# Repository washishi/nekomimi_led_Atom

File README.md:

# Nekomimi LED  for Atom
M5StackのAtomシリーズ用(AtomU/S3U以外)のネコミミ型LED基板です  
NeoPixel(WS2812)互換の1mmx1mmサイズのRGB LEDが左右に9個ずつ合計18個付いており独立して色や明るさ等を制御することができます  

## 使い方
M5Stack Atomシリーズ裏面のピンソケットに本基盤のピン部分を差し込んで取り付けます

### 使用するGPIO（ピン）

使用するGPIO端子は上記写真の赤枠のランドいずれかをはんだでショートすることにより選択できます  
[BOOTH](https://washishi.booth.pm/)等で頒布するものは上記写真のように右側上から２番目の端子が既にショートされています  
その場合の利用するGPIOは下記となります  
|Atom種別|LED Data Out|
|:--|:-:|  
|AtomS3/S3R/S3Lite/S3RCAM/S3REx/EchoS3R等S3系|G38|
|AtomLite/AtomMatrix/AtomEcho等S3系以外|G25|

## ソフトウエアでの利用について
Arduino IDE や VSCode + PlatformIO で利用する場合は
[FastLED](https://github.com/FastLED/FastLED)や[Adafruit NeoPixel](https://github.com/adafruit/Adafruit_NeoPixel)等のライブラリで利用できます  
UIFlowで利用する場合はHardwareでRGBを追加し利用するGPIOとLEDの数18を指定すれば利用できます  
その他に関しても NeoPixel を操作できるライブラリ等があれば利用できると思います  

利用上の注意点：
- ECHO BASEと併用する場合はI2Cで利用している端子をスピーカ、マイクの初期化後にI2Cでの利用を停止してから利用可能です  
- 利用するGPIOをまず出力、LOWレベルで初期化してください(行わないとLEDが意図した点灯とならない場合があります)  
&ensp;例： (GPIO38利用時)  
&emsp;(スピーカ、マイク等初期化処理)  
&emsp;Wire.end();&emsp;// ECHO BASE併用時にI2Cでの利用を終了  
&emsp;digitalWrite(GPIO38, LOW);&emsp;// GPIOを出力、LOWレベルで初期化  
&emsp;(FastLED等LEDライブラリでの初期化)

## サンプルプログラム
サンプルプログラムとして [m5stack-avatar-mic-nekomimi_led](https://github.com/washishi/m5stack-avatar-mic-nekomimi_led) を用意しました (「M5AtomS3-ECHO_BASE_PDM-LED38」をビルドしてください)  
※Takao Akaki (mongonta0716) さんの [m5stack-avatar-mic](https://github.com/mongonta0716/m5stack-avatar-mic)を改変したものとなります

音に合わせてAvatarが口パクしたり、傾いたりすると共にNekomimi LED For Atomが音量に応じて光ります    
※利用するには下記いずれかでマイクを取り付ける必要があります  
- [EchoBASE](https://docs.m5stack.com/ja/atom/Atomic%20Echo%20Base)  
- [Atom MIC](https://github.com/washishi/atom_mic)
- Grove端子に[NanoMIC](https://github.com/washishi/NanoMIC)または[Unit Mini PDM](https://docs.m5stack.com/ja/unit/pdm)  

上記のビルド済みバイナリーはM5Burnerで配布もしています  

## 回路図、BOM、ガーバデータ等
本リポジトリ schematics ディレクトリ配下に設計ファイル一式があります  

### BOM(使用部品リスト)
|番号|名称|仕様/型番|メーカー|個数|備考購入先|  
|:--|:--|:--|:-:|:-:|:-:|  
|-|基板|NekomimiLED for Atom基板<br>[ガーバデータ](schematics/production/Nekomimi_atom.zip)|-|1|[JLCPCB](https://jlcpcb.com/JPV)へ発注|
|LED1-18|マイコン内蔵RGBLED|XL-10サイズ1-0RGBC-WS2812B|XINGLIGHT|18|[LCSC](https://www.lcsc.com/product-detail/C5349953.html)|  
|R1|チップ抵抗|330Ω 0402/1005(mm)サイズ|任意|1||[マルツ](https://www.marutsu.co.jp/pc/i/856730/)<br>(通販)  
|C1-C6|チップ積層セラミックコンデンサ|0.1uF 0402/1005(mm)サイズ|任意|6|[秋月電子](https://akizukidenshi.com/catalog/g/g113377/)<br>(25個セット)|
|J1-2|ピンソケット|1P 普通のピンヘッダ(0.64mm角)が刺せる物、胴体1.5mm丸 足0.6mm丸|不明|9|[Aiexpresss](https://ja.aliexpress.com/item/1005007125065810.html)<br>E-Simpo Store<br>(500個セット)
|J1|ピンソケット用枠|[4P用モデルデータ](schematics/ピンソケット_4P.step)|-|1|3Dプリンタで出力
|J1|ピンソケット用枠|[5P用モデルデータ](schematics/ピンソケット_5P.step)|-|1|3Dプリンタで出力

#### オプション  
&emsp;頒布品では未実装の部品  
&emsp;当初ECHO BASE利用時はマイコン(CH32V003)を載せてI2Cでの利用を考えていた際の名残  
&emsp;動作未検証およびマイコンのプロクラムについては未作成  
&emsp;実装してマイコンのプログラムを書き電源だけ繋いで単独でLEDを光らしたりできるかもしれない  
|番号|名称|仕様/型番|メーカー|個数|備考購入先|  
|:--|:--|:--|:-:|:-:|:-:|  
|U1|マイコン|CH32V003J4M6|Nanjing Qinheng Microelectronics|1|[秋月電子](https://akizukidenshi.com/catalog/g/g118062/)|
|C7|チップ積層セラミックコンデンサ|0.1uF 0402/1005(mm)サイズ|任意|1|[秋月電子](https://akizukidenshi.com/catalog/g/g113377/)(25個セット)|

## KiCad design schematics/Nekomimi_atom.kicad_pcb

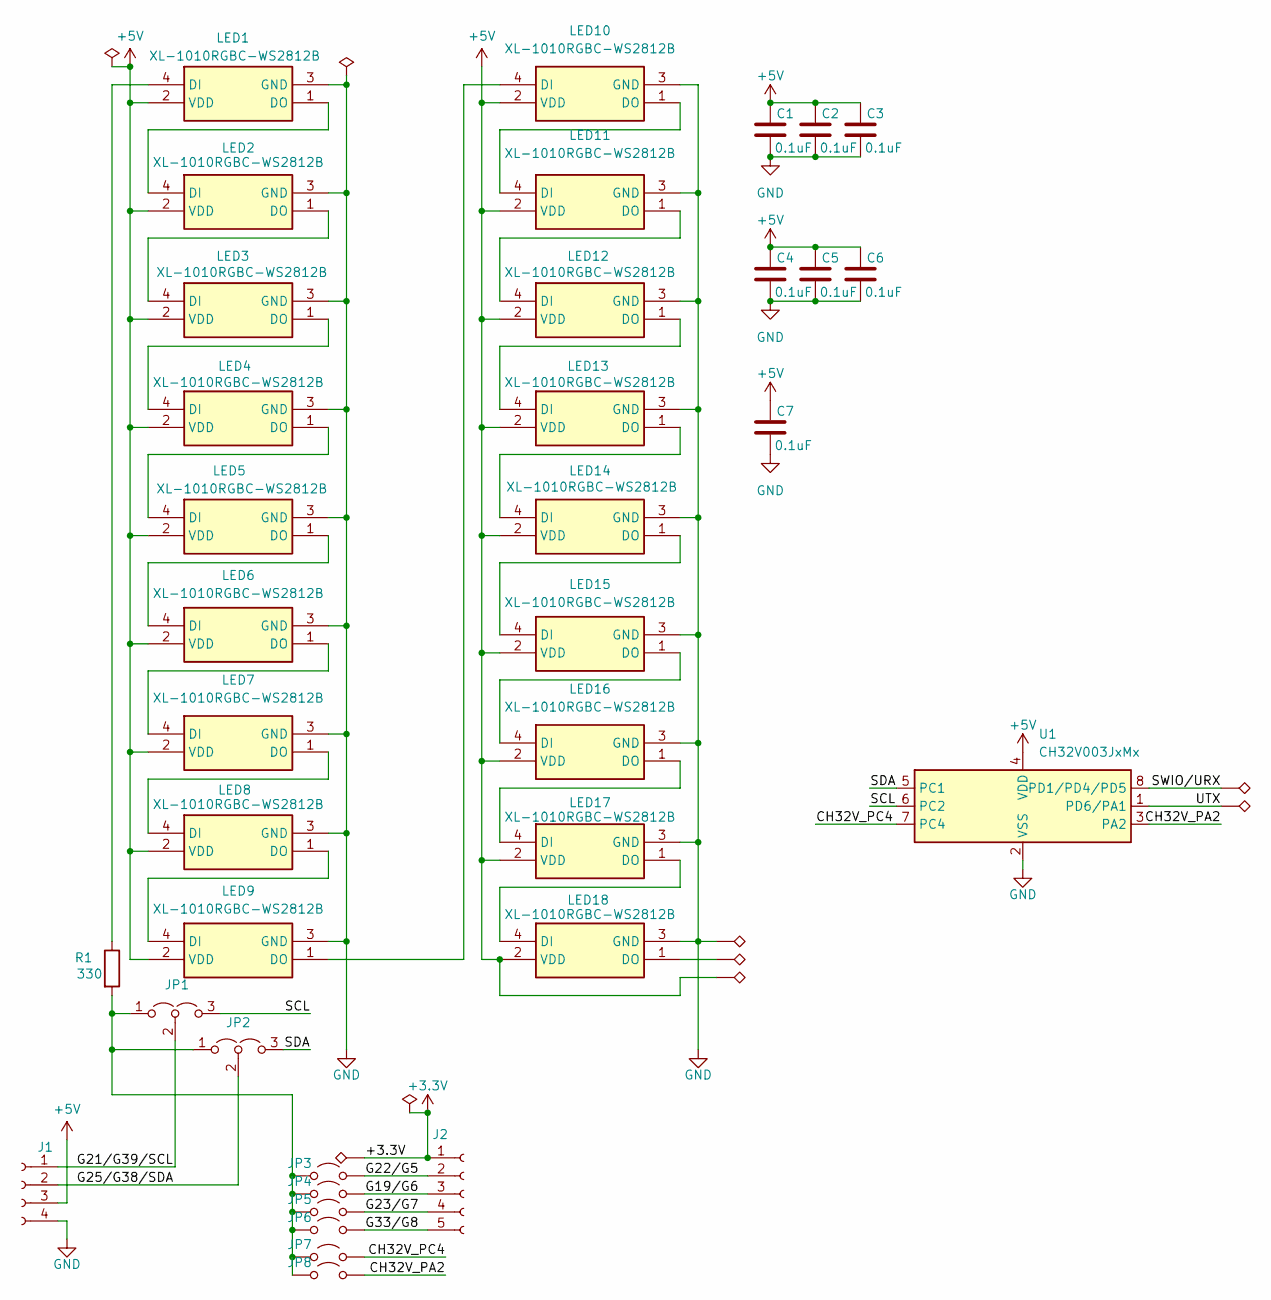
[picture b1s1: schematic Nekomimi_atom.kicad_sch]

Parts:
C1, C2, C3, C4, C5, C6, C7: 0.1uF; C_0402_1005Metric_Pad0.74x0.62mm_HandSolder
J1: PinHeader_1x04_P2.54mm_Vertical; PinSocket_1x04_P2.54mm_Vertical_Hole1.6
J2: PinHeader_1x05_P2.54mm_Vertical; PinSocket_1x05_P2.54mm_Vertical_Hole1.6
JP1, JP2: Jumper_3_Open; SolderJumper-3_P1.3mm_Open_Pad1.0x1.5mm_
JP3, JP4, JP5, JP6, JP7, JP8: Jumper_2_Open; SolderJumper-2_P1.3mm_Open_Pad1.0x1.5mm
LED1, LED2, LED3, LED4, LED5, LED6, LED7, LED8, LED9, LED10, LED11, LED12, LED13, LED14, LED15, LED16, LED17, LED18: XL-1010RGBC-WS2812B; LED XL-1010RGBC-WS2812B; Manufacturer_Part_Number WS2812C-2020; LCSC C5349953
R1: 330; R_0402_1005Metric_Pad0.72x0.64mm_HandSolder
TP1, TP4, TP5, TP6: TestPoint_Alt; TestPoint_Pad_1.0x1.0mm
TP2, TP3: TestPoint_Alt; TestPoint_THTPad_1.0x1.0mm_Drill0.8mm
U1: CH32V003JxMx; JEITA_SOIC-8_3.9x4.9mm_P1.27mm

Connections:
+3.3V: J2.1, TP4.1
+5V: C1.1, C2.1, C3.1, C4.1, C5.1, C6.1, C7.1, J1.3, LED1.2 (VDD), LED2.2 (VDD), LED3.2 (VDD), LED4.2 (VDD), LED5.2 (VDD), LED6.2 (VDD), LED7.2 (VDD), LED8.2 (VDD), LED9.2 (VDD), LED10.2 (VDD), LED11.2 (VDD), LED12.2 (VDD), LED13.2 (VDD), LED14.2 (VDD), LED15.2 (VDD), LED16.2 (VDD), LED17.2 (VDD), LED18.2 (VDD), TP6.1, U1.4 (VDD)
/CH32V_PA2: JP8.2 (B), U1.3 (PA2)
/CH32V_PC4: JP7.2 (B), U1.7 (PC4)
/G19/G6: J2.3, JP4.2 (B)
/G21/G39/SCL: J1.1, JP1.2 (C)
/G22/G5: J2.2, JP3.2 (B)
/G23/G7: J2.4, JP5.2 (B)
/G25/G38/SDA: J1.2, JP2.2 (C)
/G33/G8: J2.5, JP6.2 (B)
/SCL: JP1.3 (B), U1.6 (PC2)
/SDA: JP2.3 (B), U1.5 (PC1)
/SWIO/URX: TP2.1, U1.8 (PD1/PD4/PD5)
/UTX: TP3.1, U1.1 (PD6/PA1)
GND: C1.2, C2.2, C3.2, C4.2, C5.2, C6.2, C7.2, J1.4, LED1.3 (GND), LED2.3 (GND), LED3.3 (GND), LED4.3 (GND), LED5.3 (GND), LED6.3 (GND), LED7.3 (GND), LED8.3 (GND), LED9.3 (GND), LED10.3 (GND), LED11.3 (GND), LED12.3 (GND), LED13.3 (GND), LED14.3 (GND), LED15.3 (GND), LED16.3 (GND), LED17.3 (GND), LED18.3 (GND), TP5.1, U1.2 (VSS)
unnamed: JP1.1 (A), JP2.1 (A), JP3.1 (A), JP4.1 (A), JP5.1 (A), JP6.1 (A), JP7.1 (A), JP8.1 (A), R1.2
unnamed: LED1.4 (DI), R1.1
unnamed: LED1.1 (DO), LED2.4 (DI)
unnamed: LED2.1 (DO), LED3.4 (DI)
unnamed: LED3.1 (DO), LED4.4 (DI)
unnamed: LED4.1 (DO), LED5.4 (DI)
unnamed: LED5.1 (DO), LED6.4 (DI)
unnamed: LED6.1 (DO), LED7.4 (DI)
unnamed: LED7.1 (DO), LED8.4 (DI)
unnamed: LED8.1 (DO), LED9.4 (DI)
unnamed: LED9.1 (DO), LED10.4 (DI)
unnamed: LED10.1 (DO), LED11.4 (DI)
unnamed: LED11.1 (DO), LED12.4 (DI)
unnamed: LED12.1 (DO), LED13.4 (DI)
unnamed: LED13.1 (DO), LED14.4 (DI)
unnamed: LED14.1 (DO), LED15.4 (DI)
unnamed: LED15.1 (DO), LED16.4 (DI)
unnamed: LED16.1 (DO), LED17.4 (DI)
unnamed: LED17.1 (DO), LED18.4 (DI)
unnamed: LED18.1 (DO), TP1.1

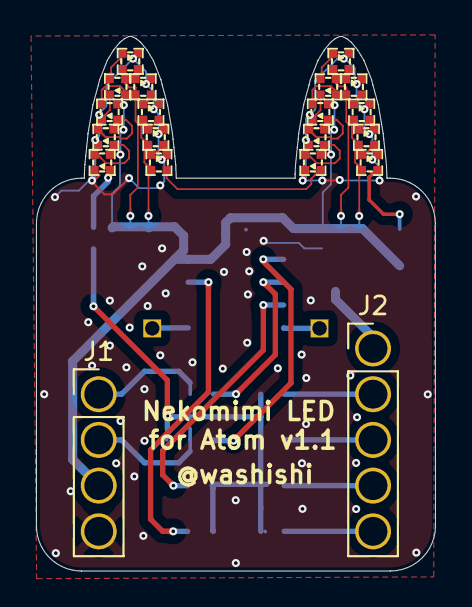
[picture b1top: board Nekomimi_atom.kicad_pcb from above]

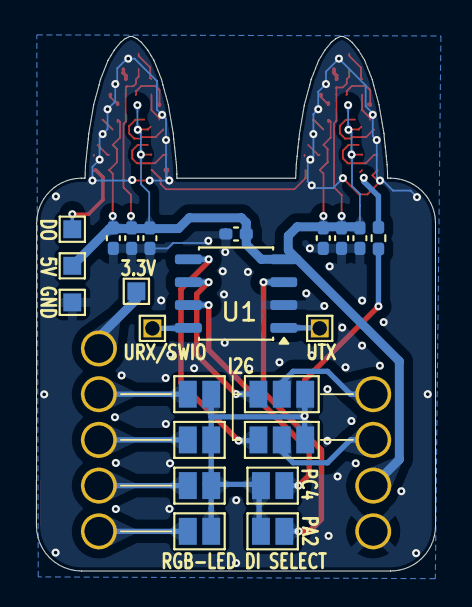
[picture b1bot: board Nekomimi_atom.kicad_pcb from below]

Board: 2 copper layers, 22.2 x 29.7 mm, 43 parts (23 on the bottom side), 35 nets.

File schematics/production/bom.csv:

Designator,Footprint,Quantity,Value,LCSC Part #
"C1, C2, C3, C4, C5, C6, C7",0402,7,0.1uF,
J1,PinSocket_1x04_P2.54mm_Vertical_Hole1.6,1,PinHeader_1x04_P2.54mm_Vertical,
J2,PinSocket_1x05_P2.54mm_Vertical_Hole1.6,1,PinHeader_1x05_P2.54mm_Vertical,
"JP3, JP4, JP5, JP6, JP7, JP8",SolderJumper-2_P1.3mm_Open_Pad1.0x1.5mm,6,Jumper_2_Open,
"LED1, LED10, LED11, LED12, LED13, LED14, LED15, LED16, LED17, LED18, LED2, LED3, LED4, LED5, LED6, LED7, LED8, LED9",LED XL-1010RGBC-WS2812B,18,XL-1010RGBC-WS2812B,C5349953
R1,0402,1,330,
"TP1, TP4, TP5, TP6",TestPoint_Pad_1.0x1.0mm,4,TestPoint_Alt,
"TP2, TP3",TestPoint_THTPad_1.0x1.0mm_Drill0.8mm,2,TestPoint_Alt,
U1,JEITA_SOIC-8_3.9x4.9mm_P1.27mm,1,CH32V003JxMx,

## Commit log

2026-02-08 Update README for Nekomimi LED for Atom
